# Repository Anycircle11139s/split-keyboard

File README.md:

# split-keyboard

Readme time...

I created a split keyboard, because I really enjoyed making the hackpad and I spend a lot of time on my computer and don't wanna get carpal tunnel. I spent a really long time making the split keyboard and it's a bit basic, but I like it. 

This is the code, its pretty simple, but I didn't want to make it too complex as it is my first time working with zmk (I used kmk for the hackpad before)

This is my PCB, I spent a while placing the keys in a format that I liked, but I spet a lot longer routing the thing. I lowkenuinely spent like 7 hours just routing it :I

Here, I have the case, I'm pretty proud of it because there was no tutorial and I had to wing it, but it still turned out pretty well.

The schematic was pretty fun, I made hierarchial sheets and a rlly big keyboard matrix, it was overall pretty easy (the schematic)

BOM:

|Name                              |Purpose                                                              |Quantity|Total Cost (USD)|Link                                                                                                                                                                                                                                                                                                                                                                                                                                                                                                                                                                                                                                                                                                                              |Distributor    |
|----------------------------------|---------------------------------------------------------------------|--------|----------------|----------------------------------------------------------------------------------------------------------------------------------------------------------------------------------------------------------------------------------------------------------------------------------------------------------------------------------------------------------------------------------------------------------------------------------------------------------------------------------------------------------------------------------------------------------------------------------------------------------------------------------------------------------------------------------------------------------------------------------|---------------|
|Soldering iron tip cleaner        |To get solder off my soldering iron when soldering the split keyboard|1       |2.51            |https://www.aliexpress.com/item/1005011767599627.html?spm=a2g0o.productlist.main.27.7328c2f2shmCH7&utparam-url=scene%3Asearch%7Cquery_from%3Apc_back_same_best%7Cx_object_id%3A1005011767599627%7C_p_origin_prod%3A&algo_pvid=cc685b5f-8751-4102-90f8-53ff884c5232&algo_exp_id=cc685b5f-8751-4102-90f8-53ff884c5232&pdp_ext_f=%7B%22order%22%3A%229%22%2C%22fromPage%22%3A%22search%22%7D&pdp_npi=6%40dis%21USD%215.70%212.51%21%21%2138.78%2117.11%21%402101d6ff17761259441958065e0e06%2112000056487277700%21sea%21AU%217402515296%21X%211%210%21n_tag%3A-29911%3Bd%3Aef1e07f3%3Bm03_new_user%3A-29895%3BpisId%3A5000000204651200                                                                                                |ali-express    |
|Tweezers                          |So i can place small stuff on a board                                |1       |3.80            |https://www.aliexpress.com/item/1005008096741092.html?spm=a2g0o.productlist.main.9.4c38be661axNMB&algo_pvid=bf336258-f5d2-4640-9eb9-c3400287f7d3&algo_exp_id=bf336258-f5d2-4640-9eb9-c3400287f7d3-8&pdp_ext_f=%7B%22order%22%3A%22112%22%2C%22eval%22%3A%221%22%2C%22fromPage%22%3A%22search%22%7D&pdp_npi=6%40dis%21USD%2110.78%213.77%21%21%2173.30%2125.65%21%402101d97817761258015788989ee059%2112000043710740481%21sea%21AU%217402515296%21X%211%210%21n_tag%3A-29911%3Bd%3Aef1e07f3%3Bm03_new_user%3A-29895&curPageLogUid=Mt26q52kHGuW&utparam-url=scene%3Asearch%7Cquery_from%3A%7Cx_object_id%3A1005008096741092%7C_p_origin_prod%3A                                                                                      |Ali-express    |
|Wick                              |So if I make mistakes i can suck up the solder                       |1       |1.90            |https://www.aliexpress.com/item/1005005111965242.html?spm=a2g0o.productlist.main.3.1f37DXflDXfl2M&algo_pvid=1c46e9b7-bb70-4c58-9f79-255ede25b328&algo_exp_id=1c46e9b7-bb70-4c58-9f79-255ede25b328-2&pdp_ext_f=%7B%22order%22%3A%2245%22%2C%22eval%22%3A%221%22%2C%22fromPage%22%3A%22search%22%7D&pdp_npi=6%40dis%21USD%211.88%211.88%21%21%211.88%211.88%21%402101c59117761256926156551e99f7%2112000031701100437%21sea%21AU%217402515296%21X%211%210%21n_tag%3A-29911%3Bd%3Aef1e07f3%3Bm03_new_user%3A-29895&curPageLogUid=mRkJDXXkg8eW&utparam-url=scene%3Asearch%7Cquery_from%3A%7Cx_object_id%3A1005005111965242%7C_p_origin_prod%3A                                                                                          |Ali-express    |
|Helping hands                     |to allow me to solder all the stuff                                  |1       |1.50            |https://www.aliexpress.com/item/1005011766151305.html?spm=a2g0o.productlist.main.1.481cVm5XVm5Xzy&algo_pvid=d26a067d-f485-4524-b116-90d984bdbd17&algo_exp_id=d26a067d-f485-4524-b116-90d984bdbd17-0&pdp_ext_f=%7B%22order%22%3A%2227%22%2C%22eval%22%3A%221%22%2C%22fromPage%22%3A%22search%22%7D&pdp_npi=6%40dis%21USD%2112.18%210.99%21%21%2182.78%216.69%21%402103212b17761255550781608e26da%2112000056480873900%21sea%21AU%217402515296%21X%211%210%21n_tag%3A-29911%3Bd%3Aef1e07f3%3Bm03_new_user%3A-29895%3BpisId%3A5000000204047332&curPageLogUid=XIfqg1kNm8Ci&utparam-url=scene%3Asearch%7Cquery_from%3A%7Cx_object_id%3A1005011766151305%7C_p_origin_prod%3A                                                             |Ali-express    |
|M3X4X5 Heat Insert Nut M3 Threaded|for inseting pcb t case                                              |50      |2.88            |https://www.aliexpress.com/item/1005010775775055.html?spm=a2g0o.productlist.main.5.8270VWLgVWLgfU&algo_pvid=5d20a7d9-fe9d-46a3-99e0-bb8002b99240&algo_exp_id=5d20a7d9-fe9d-46a3-99e0-bb8002b99240-4&pdp_ext_f=%7B%22order%22%3A%2227%22%2C%22eval%22%3A%221%22%2C%22fromPage%22%3A%22search%22%7D&pdp_npi=6%40dis%21USD%216.95%212.88%21%21%2147.28%2119.58%21%4021030a6217761254961261252e2bd4%2112000053469867927%21sea%21AU%217402515296%21X%211%210%21n_tag%3A-29911%3Bd%3Aef1e07f3%3Bm03_new_user%3A-29895%3BpisId%3A5000000204651200&curPageLogUid=NCSO1LTRLGJM&utparam-url=scene%3Asearch%7Cquery_from%3A%7Cx_object_id%3A1005010775775055%7C_p_origin_prod%3A                                                             |Ali-express    |
|Case printing and shipping        |The case                                                             |1       |7.00            |                                                                                                                                                                                                                                                                                                                                                                                                                                                                                                                                                                                                                                                                                                                                  |Printing Legion|
|PCB                               |The board which the components go on                                 |1       |31.50           |                                                                                                                                                                                                                                                                                                                                                                                                                                                                                                                                                                                                                                                                                                                                  |JLCPCB         |
|xiao nRF52840                     |microcontroller                                                      |2       |13.62           |https://www.aliexpress.com/item/1005006988954136.html?spm=a2g0o.productlist.main.1.59c9qZFNqZFNqM&algo_pvid=59a296da-82e0-4b65-b5b5-be68fc8709da&algo_exp_id=59a296da-82e0-4b65-b5b5-be68fc8709da-0&pdp_ext_f=%7B%22order%22%3A%221989%22%2C%22eval%22%3A%221%22%2C%22fromPage%22%3A%22search%22%7D&pdp_npi=6%40dis%21USD%2135.89%2113.62%21%21%21244.00%2192.57%21%402101eecd17760577752436478e83e2%2112000042942288178%21sea%21AU%217402515296%21X%211%210%21n_tag%3A-29911%3Bd%3Aef1e07f3%3Bm03_new_user%3A-29895%3BpisId%3A5000000204047332&curPageLogUid=Ylmc5XGHF4Vx&utparam-url=scene%3Asearch%7Cquery_from%3A%7Cx_object_id%3A1005006988954136%7C_p_origin_prod%3A                                                        |Ali-express    |
|Diodes                            |to prevent ghosting                                                  |100     |0.86            |https://www.aliexpress.com/item/32947233235.html?spm=a2g0o.productlist.main.4.d94d2d8bu6I5TB&aem_p4p_detail=2026041222120919273074358951920002316458&algo_pvid=8d9d299d-7065-4467-aa40-a1696623dfeb&algo_exp_id=8d9d299d-7065-4467-aa40-a1696623dfeb-3&pdp_ext_f=%7B%22order%22%3A%2274%22%2C%22eval%22%3A%221%22%2C%22fromPage%22%3A%22search%22%7D&pdp_npi=6%40dis%21USD%210.86%210.82%21%21%210.86%210.82%21%402101eee917760571299056119ee961%2166204047427%21sea%21AU%210%21ABX%211%210%21n_tag%3A-29910%3Bd%3Aef1e07f3%3Bm03_new_user%3A-29895&curPageLogUid=F7ZBmq9h6Im1&utparam-url=scene%3Asearch%7Cquery_from%3A%7Cx_object_id%3A32947233235%7C_p_origin_prod%3A&search_p4p_id=2026041222120919273074358951920002316458_1|Ali-express    |
|M2 screws                         |to hold it together                                                  |50      |1.90            |https://www.aliexpress.com/item/1005005070119421.html?spm=a2g0o.productlist.main.2.346548ab4NZzwl&algo_pvid=d25a0667-c54a-4cf3-a1e0-3a0220de0126&algo_exp_id=d25a0667-c54a-4cf3-a1e0-3a0220de0126-1&pdp_ext_f=%7B%22order%22%3A%2247544%22%2C%22spu_best_type%22%3A%22price%22%2C%22eval%22%3A%221%22%2C%22fromPage%22%3A%22search%22%7D&pdp_npi=6%40dis%21USD%212.54%210.99%21%21%212.54%210.99%21%402103274e17760568275421650e83f3%2112000031519353295%21sea%21AU%210%21ABX%211%210%21n_tag%3A-29910%3Bd%3Aef1e07f3%3Bm03_new_user%3A-29895%3BpisId%3A5000000203295528&curPageLogUid=QL9hN1rPFrTw&utparam-url=scene%3Asearch%7Cquery_from%3A%7Cx_object_id%3A1005005070119421%7C_p_origin_prod%3A                               |Ali-express    |
|Keycaps                           |to cover the keys                                                    |124     |3.93            |https://www.aliexpress.com/item/1005007360831985.html                                                                                                                                                                                                                                                                                                                                                                                                                                                                                                                                                                                                                                                                             |Ali-express    |
|Switches                          |Buttons for keyboard                                                 |110     |16.00           |https://www.aliexpress.com/item/1005004285423123.html                                                                                                                                                                                                                                                                                                                                                                                                                                                                                                                                                                                                                                                                             |Ali-express    |

<br>

<br>

Building keyboard:
<br>
So I spent a rlly long time sodlering everything together and after a couple bugs and troubleshooting, I finally got it working. I'm really proud of my design and I can't wait to show this off to all my friends and family!
<br>
<br>

https://github.com/user-attachments/assets/18d752bb-31d4-4ef4-a61a-be9153cc65bb

https://github.com/user-attachments/assets/6f350401-69de-47bb-a7fa-8a00cfc4a692

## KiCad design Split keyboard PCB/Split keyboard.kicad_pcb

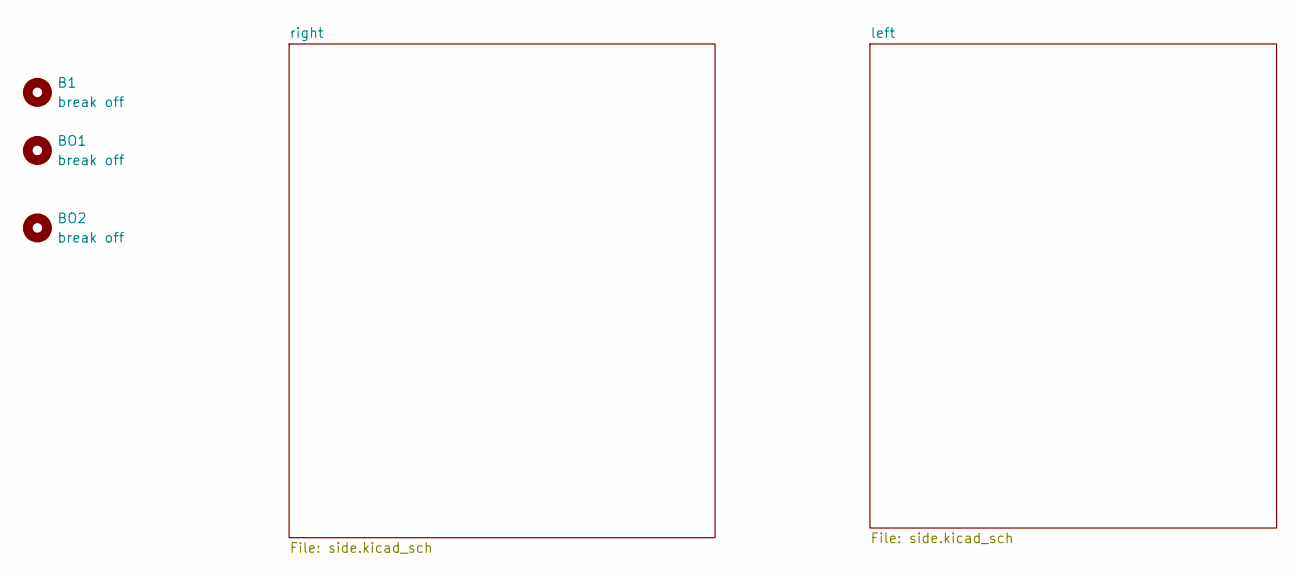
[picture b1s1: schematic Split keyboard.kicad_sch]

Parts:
B1: break off; mouse-bite-1mm-slot
BO1, BO2: break off; mouse-bite-1mm-slot

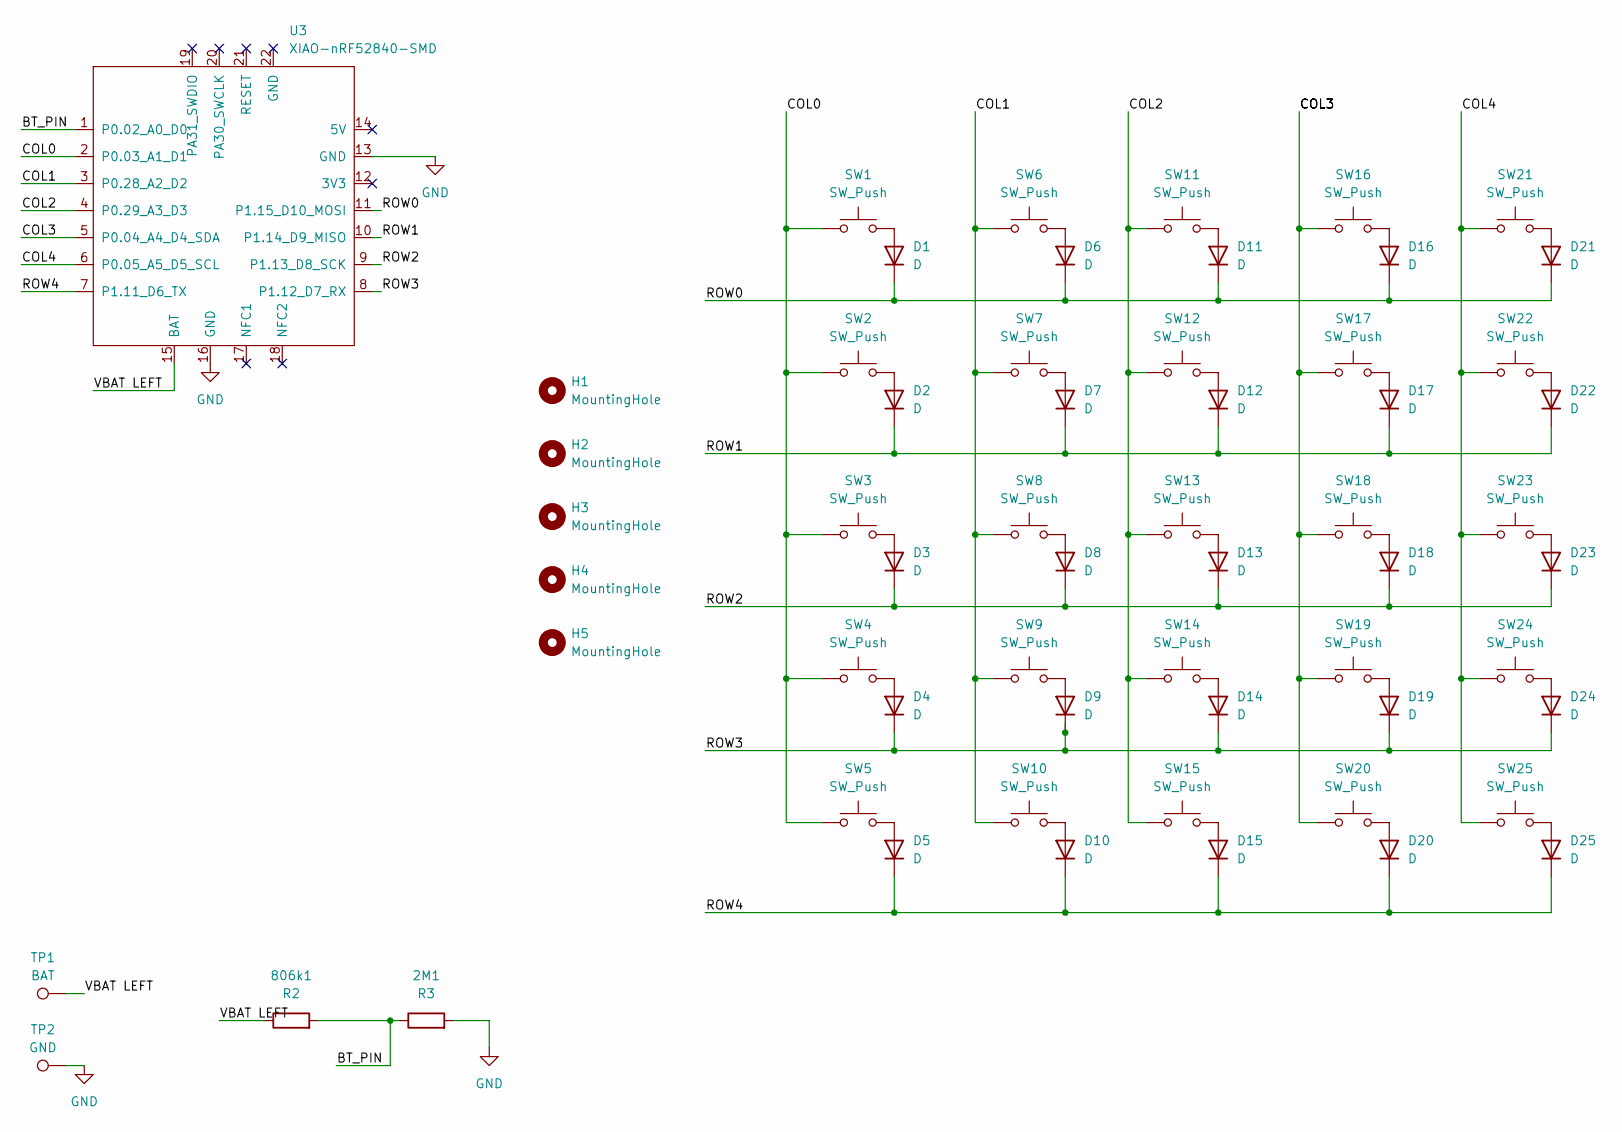
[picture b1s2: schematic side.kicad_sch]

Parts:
2M1: R3; R_0805_2012Metric
806k1: R2; R_0805_2012Metric
D1, D2, D3, D4, D5, D6, D7, D8, D9, D10, D11, D12, D13, D14, D15, D16, D17, D18, D19, D20, D21, D22, D23, D24, D25: D; D_DO-35_SOD27_P7.62mm_Horizontal
H1, H2, H3, H4, H5: MountingHole; MountingHole_2.2mm_M2_DIN965_Pad
SW1, SW2, SW3, SW4, SW5, SW6, SW7, SW8, SW9, SW10, SW11, SW12, SW13, SW14, SW15, SW16, SW17, SW18, SW19, SW20, SW21, SW22, SW23, SW24, SW25: SW_Push; SW_Cherry_MX_1.00u_PCB
TP1: BAT; TestPoint_Pad_D2.0mm
TP2: GND; TestPoint_Pad_D2.0mm
U3: XIAO-nRF52840-SMD; Modified XIAO nRF52840 SMD

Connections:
/left/BT_PIN: 2M1.1, 806k1.2, U3.1 (P0.02_A0_D0)
/left/COL0: SW1.1, SW2.1, SW3.1, SW4.1, SW5.1, U3.2 (P0.03_A1_D1)
/left/COL1: SW6.1, SW7.1, SW8.1, SW9.1, SW10.1, U3.3 (P0.28_A2_D2)
/left/COL2: SW11.1, SW12.1, SW13.1, SW14.1, SW15.1, U3.4 (P0.29_A3_D3)
/left/COL3: SW16.1, SW17.1, SW18.1, SW19.1, SW20.1, U3.5 (P0.04_A4_D4_SDA)
/left/COL4: SW21.1, SW22.1, SW23.1, SW24.1, SW25.1, U3.6 (P0.05_A5_D5_SCL)
/left/ROW0: D1.1 (K), D6.1 (K), D11.1 (K), D16.1 (K), D21.1 (K), U3.11 (P1.15_D10_MOSI)
/left/ROW1: D2.1 (K), D7.1 (K), D12.1 (K), D17.1 (K), D22.1 (K), U3.10 (P1.14_D9_MISO)
/left/ROW2: D3.1 (K), D8.1 (K), D13.1 (K), D18.1 (K), D23.1 (K), U3.9 (P1.13_D8_SCK)
/left/ROW3: D4.1 (K), D9.1 (K), D14.1 (K), D19.1 (K), D24.1 (K), U3.8 (P1.12_D7_RX)
/left/ROW4: D5.1 (K), D10.1 (K), D15.1 (K), D20.1 (K), D25.1 (K), U3.7 (P1.11_D6_TX)
/left/VBAT LEFT: 806k1.1, TP1.1, U3.15 (BAT)
GND: 2M1.2, TP2.1, U3.13 (GND), U3.16 (GND); also elsewhere on the board
unnamed: D1.2 (A), SW1.2
unnamed: D2.2 (A), SW2.2
unnamed: D3.2 (A), SW3.2
unnamed: D4.2 (A), SW4.2
unnamed: D5.2 (A), SW5.2
unnamed: D6.2 (A), SW6.2
unnamed: D7.2 (A), SW7.2
unnamed: D8.2 (A), SW8.2
unnamed: D9.2 (A), SW9.2
unnamed: D10.2 (A), SW10.2
unnamed: D11.2 (A), SW11.2
unnamed: D12.2 (A), SW12.2
unnamed: D13.2 (A), SW13.2
unnamed: D14.2 (A), SW14.2
unnamed: D15.2 (A), SW15.2
unnamed: D16.2 (A), SW16.2
unnamed: D17.2 (A), SW17.2
unnamed: D18.2 (A), SW18.2
unnamed: D19.2 (A), SW19.2
unnamed: D20.2 (A), SW20.2
unnamed: D21.2 (A), SW21.2
unnamed: D22.2 (A), SW22.2
unnamed: D23.2 (A), SW23.2
unnamed: D24.2 (A), SW24.2
unnamed: D25.2 (A), SW25.2

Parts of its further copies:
D26, D27, D28, D29, D30, D31, D32, D33, D34, D35, D36, D37, D38, D39, D40, D41, D42, D43, D44, D45, D46, D47, D48, D49, D50: D; D_DO-35_SOD27_P7.62mm_Horizontal
H6, H7, H8, H9, H10: MountingHole; MountingHole_2.2mm_M2_DIN965_Pad
R1: R2; R_0805_2012Metric
R2: R3; R_0805_2012Metric
SW26, SW27, SW28, SW29, SW30, SW31, SW32, SW33, SW34, SW35, SW36, SW37, SW38, SW39, SW40, SW41, SW42, SW43, SW44, SW45, SW46, SW47, SW48, SW49, SW50: SW_Push; SW_Cherry_MX_1.00u_PCB
TP3: BAT; TestPoint_Pad_D2.0mm
TP4: GND; TestPoint_Pad_D2.0mm
U4: XIAO-nRF52840-SMD; Modified XIAO nRF52840 SMD

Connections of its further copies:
/right/BT_PIN: R1.2, R2.1, U4.1 (P0.02_A0_D0)
/right/COL0: SW26.1, SW27.1, SW28.1, SW29.1, SW30.1, U4.2 (P0.03_A1_D1)
/right/COL1: SW31.1, SW32.1, SW33.1, SW34.1, SW35.1, U4.3 (P0.28_A2_D2)
/right/COL2: SW36.1, SW37.1, SW38.1, SW39.1, SW40.1, U4.4 (P0.29_A3_D3)
/right/COL3: SW41.1, SW42.1, SW43.1, SW44.1, SW45.1, U4.5 (P0.04_A4_D4_SDA)
/right/COL4: SW46.1, SW47.1, SW48.1, SW49.1, SW50.1, U4.6 (P0.05_A5_D5_SCL)
/right/ROW0: D26.1 (K), D31.1 (K), D36.1 (K), D41.1 (K), D46.1 (K), U4.11 (P1.15_D10_MOSI)
/right/ROW1: D27.1 (K), D32.1 (K), D37.1 (K), D42.1 (K), D47.1 (K), U4.10 (P1.14_D9_MISO)
/right/ROW2: D28.1 (K), D33.1 (K), D38.1 (K), D43.1 (K), D48.1 (K), U4.9 (P1.13_D8_SCK)
/right/ROW3: D29.1 (K), D34.1 (K), D39.1 (K), D44.1 (K), D49.1 (K), U4.8 (P1.12_D7_RX)
/right/ROW4: D30.1 (K), D35.1 (K), D40.1 (K), D45.1 (K), D50.1 (K), U4.7 (P1.11_D6_TX)
/right/VBAT LEFT: R1.1, TP3.1, U4.15 (BAT)
GND: R2.2, TP4.1, U4.13 (GND), U4.16 (GND); also elsewhere on the board
unnamed: D26.2 (A), SW26.2
unnamed: D27.2 (A), SW27.2
unnamed: D28.2 (A), SW28.2
unnamed: D29.2 (A), SW29.2
unnamed: D30.2 (A), SW30.2
unnamed: D31.2 (A), SW31.2
unnamed: D32.2 (A), SW32.2
unnamed: D33.2 (A), SW33.2
unnamed: D34.2 (A), SW34.2
unnamed: D35.2 (A), SW35.2
unnamed: D36.2 (A), SW36.2
unnamed: D37.2 (A), SW37.2
unnamed: D38.2 (A), SW38.2
unnamed: D39.2 (A), SW39.2
unnamed: D40.2 (A), SW40.2
unnamed: D41.2 (A), SW41.2
unnamed: D42.2 (A), SW42.2
unnamed: D43.2 (A), SW43.2
unnamed: D44.2 (A), SW44.2
unnamed: D45.2 (A), SW45.2
unnamed: D46.2 (A), SW46.2
unnamed: D47.2 (A), SW47.2
unnamed: D48.2 (A), SW48.2
unnamed: D49.2 (A), SW49.2
unnamed: D50.2 (A), SW50.2

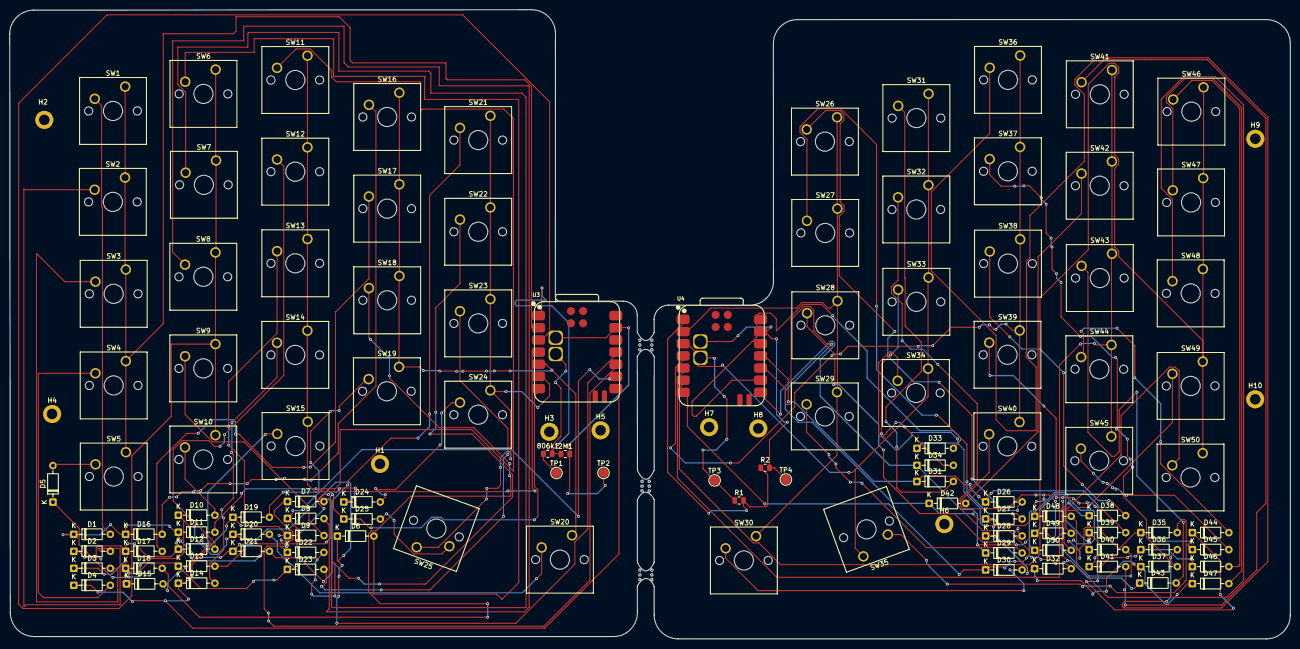
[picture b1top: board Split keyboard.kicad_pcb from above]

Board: 2 copper layers, 267.4 x 131.4 mm, 123 parts (0 on the bottom side), 75 nets.
